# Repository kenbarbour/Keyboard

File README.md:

# Keyboard
Source files for building some mechanical keyboards

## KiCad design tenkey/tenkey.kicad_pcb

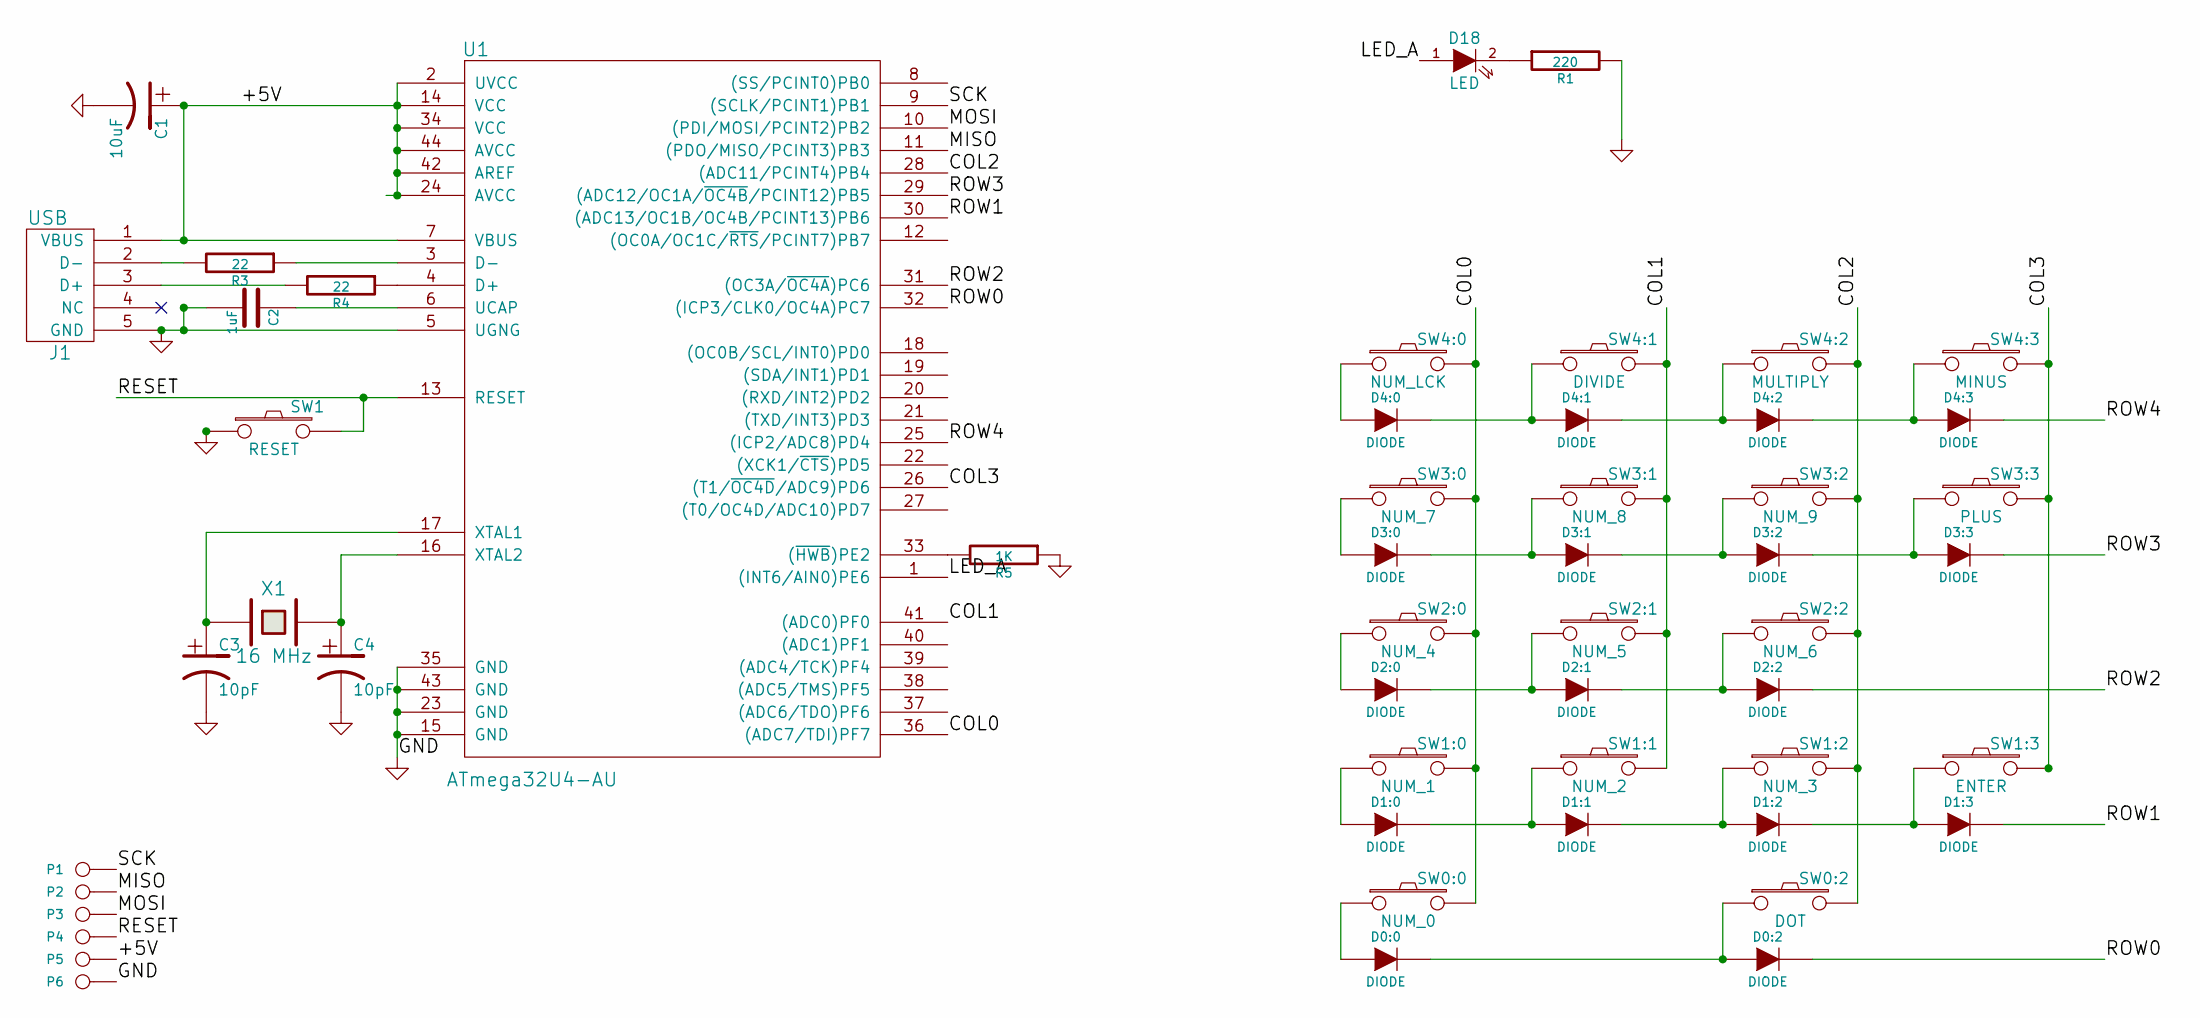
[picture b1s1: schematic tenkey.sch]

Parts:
C1: 10uF
C2: 1uF
C3, C4: 10pF
D0:0, D0:2, D1:0, D1:1, D1:2, D1:3, D2:0, D2:1, D2:2, D3:0, D3:1, D3:2, D3:3, D4:0, D4:1, D4:2, D4:3: DIODE
D18: LED
J1: USB
P1: SCK
P2: MISO
P3: MOSI
P4: RESET
P5: 5V
P6: GND
R1: 220
R3, R4: 22
R5: 1K
SW0:0: NUM_0
SW0:2: DOT
SW1: RESET
SW1:0: NUM_1
SW1:1: NUM_2
SW1:2: NUM_3
SW1:3: ENTER
SW2:0: NUM_4
SW2:1: NUM_5
SW2:2: NUM_6
SW3:0: NUM_7
SW3:1: NUM_8
SW3:2: NUM_9
SW3:3: PLUS
SW4:0: NUM_LCK
SW4:1: DIVIDE
SW4:2: MULTIPLY
SW4:3: MINUS
U1: ATmega32U4-AU
X1: 16 MHz

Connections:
/+5V: C1.1, J1.1 (VBUS), P5.1, U1.2 (UVCC), U1.7 (VBUS), U1.14 (VCC), U1.24 (AVCC), U1.34 (VCC), U1.42 (AREF), U1.44 (AVCC)
/COL0: SW0:0.2, SW1:0.2, SW2:0.2, SW3:0.2, SW4:0.2, U1.36 ((ADC7/TDI)PF7)
/COL1: SW1:1.2, SW2:1.2, SW3:1.2, SW4:1.2, U1.41 ((ADC0)PF0)
/COL2: SW0:2.2, SW1:2.2, SW2:2.2, SW3:2.2, SW4:2.2, U1.28 ((ADC11/PCINT4)PB4)
/COL3: SW1:3.2, SW3:3.2, SW4:3.2, U1.26 ((T1/~OC4D~/ADC9)PD6)
/LED_A: D18.1 (A), U1.1 ((INT6/AIN0)PE6)
/MISO: P2.1, U1.11 ((PDO/MISO/PCINT3)PB3)
/MOSI: P3.1, U1.10 ((PDI/MOSI/PCINT2)PB2)
/RESET: P4.1, SW1.2, U1.13 (RESET)
/ROW0: D0:2.2 (K), U1.32 ((ICP3/CLK0/OC4A)PC7)
/ROW1: D1:3.2 (K), U1.30 ((ADC13/OC1B/OC4B/PCINT13)PB6)
/ROW2: D2:2.2 (K), U1.31 ((OC3A/~OC4A~)PC6)
/ROW3: D3:3.2 (K), U1.29 ((ADC12/OC1A/~OC4B~/PCINT12)PB5)
/ROW4: D4:3.2 (K), U1.25 ((ICP2/ADC8)PD4)
/SCK: P1.1, U1.9 ((SCLK/PCINT1)PB1)
GND: C1.2, C2.2, C3.2, C4.2, J1.5 (GND), P6.1, R1.2, R5.1, SW1.1, U1.5 (UGNG), U1.15 (GND), U1.23 (GND), U1.35 (GND), U1.43 (GND)
unnamed: C2.1, U1.6 (UCAP)
unnamed: C3.1, U1.17 (XTAL1), X1.1
unnamed: C4.1, U1.16 (XTAL2), X1.2
unnamed: D0:0.1 (A), SW0:0.1
unnamed: D0:0.2 (K), D0:2.1 (A), SW0:2.1
unnamed: D1:0.1 (A), SW1:0.1
unnamed: D1:0.2 (K), D1:1.1 (A), SW1:1.1
unnamed: D1:1.2 (K), D1:2.1 (A), SW1:2.1
unnamed: D1:2.2 (K), D1:3.1 (A), SW1:3.1
unnamed: D2:0.1 (A), SW2:0.1
unnamed: D2:0.2 (K), D2:1.1 (A), SW2:1.1
unnamed: D2:1.2 (K), D2:2.1 (A), SW2:2.1
unnamed: D3:0.1 (A), SW3:0.1
unnamed: D3:0.2 (K), D3:1.1 (A), SW3:1.1
unnamed: D3:1.2 (K), D3:2.1 (A), SW3:2.1
unnamed: D3:2.2 (K), D3:3.1 (A), SW3:3.1
unnamed: D4:0.1 (A), SW4:0.1
unnamed: D4:0.2 (K), D4:1.1 (A), SW4:1.1
unnamed: D4:1.2 (K), D4:2.1 (A), SW4:2.1
unnamed: D4:2.2 (K), D4:3.1 (A), SW4:3.1
unnamed: D18.2 (K), R1.1
unnamed: J1.2 (D-), R3.2
unnamed: J1.3 (D+), R4.2
unnamed: R3.1, U1.3 (D-)
unnamed: R4.1, U1.4 (D+)
unnamed: R5.2, U1.33 ((~HWB~)PE2)

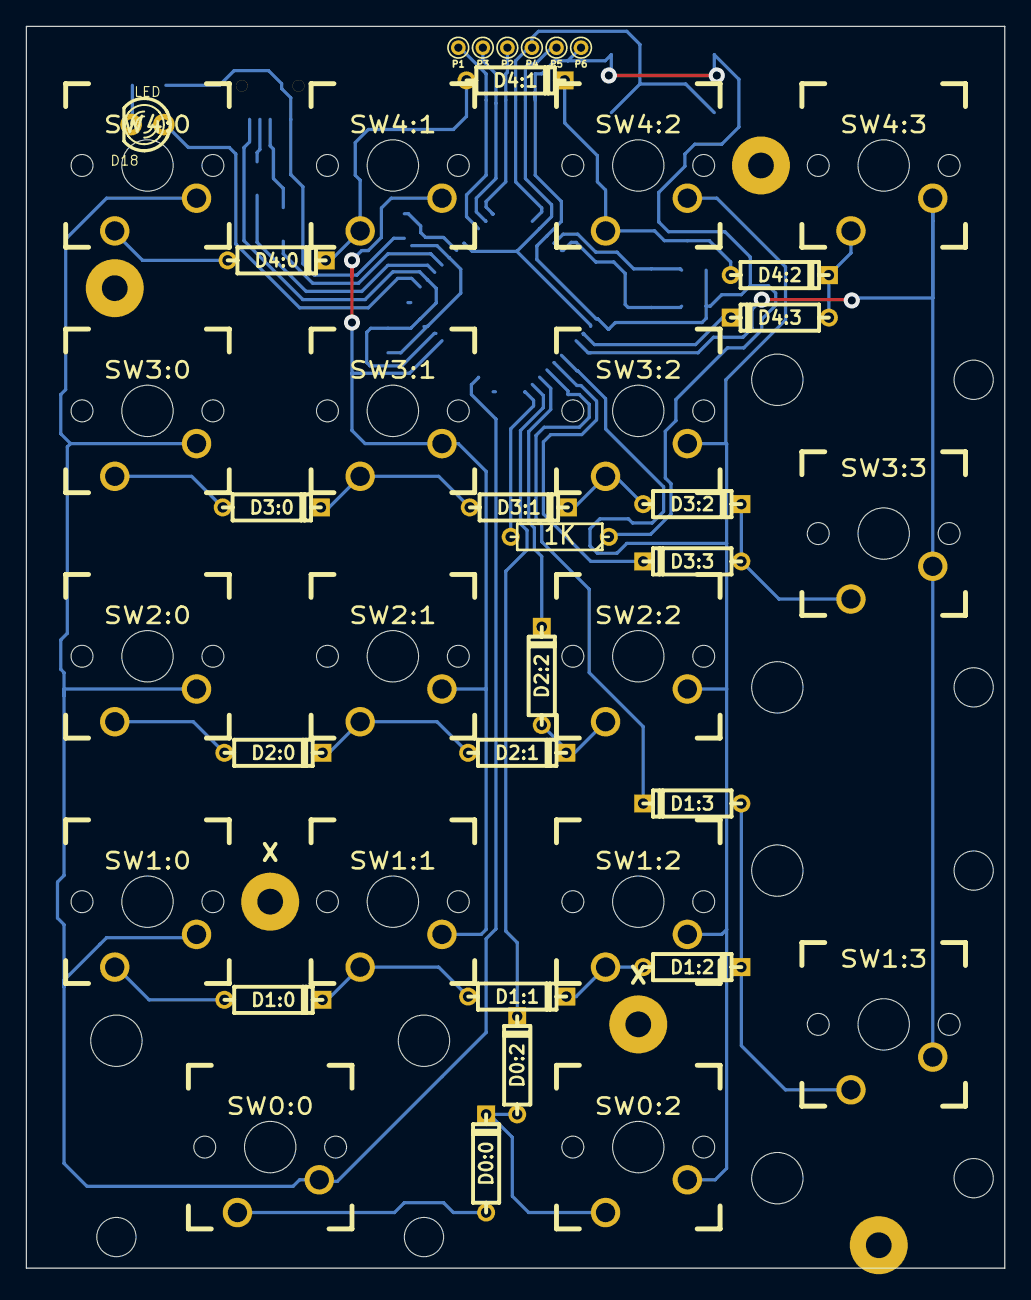
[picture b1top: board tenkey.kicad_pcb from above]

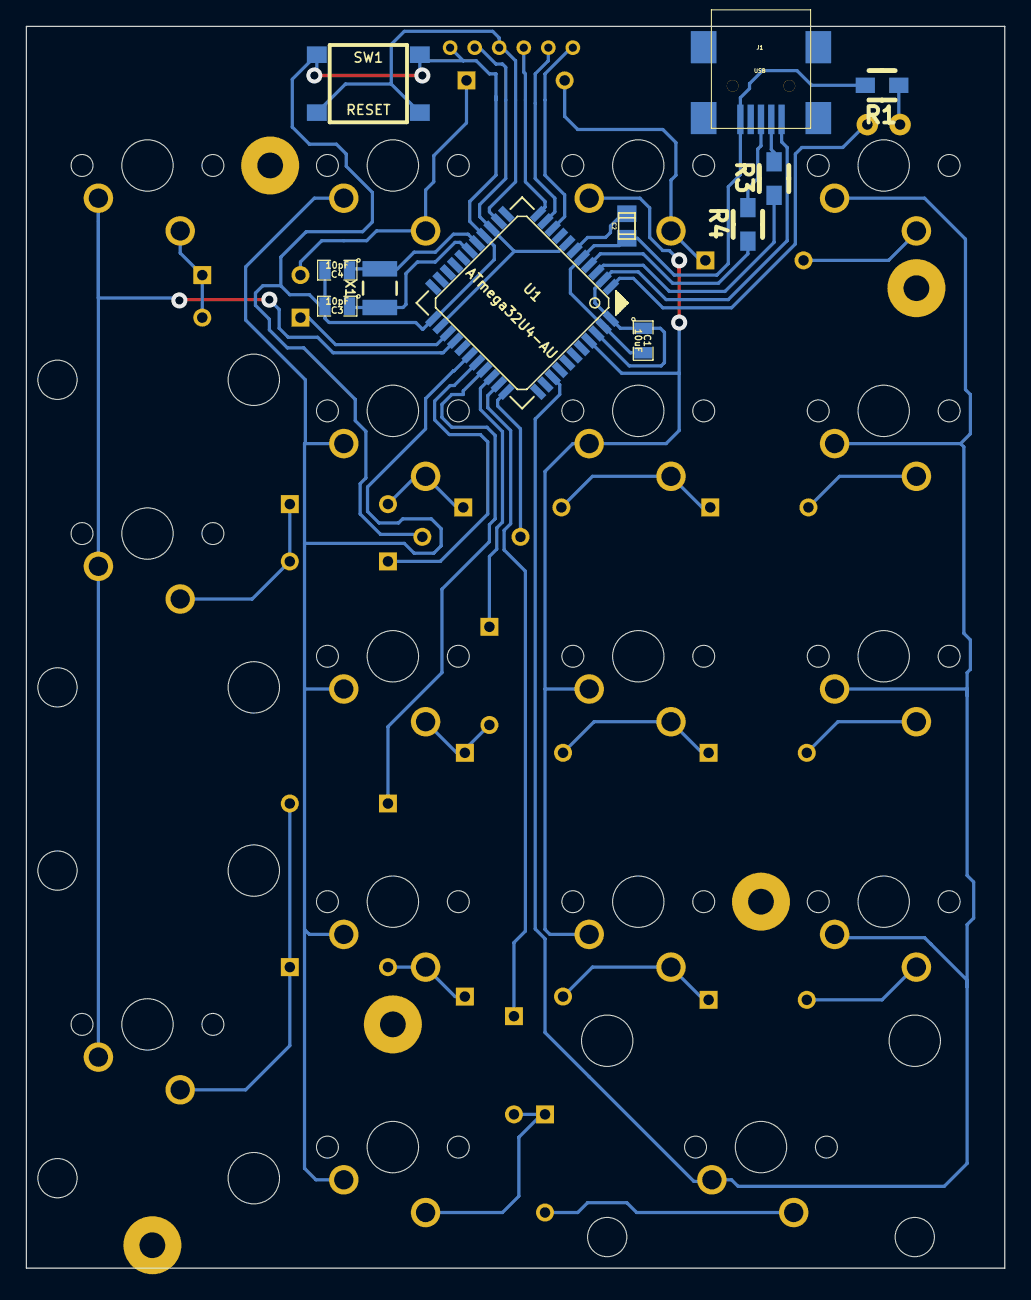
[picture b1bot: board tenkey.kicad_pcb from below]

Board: 2 copper layers, 75.9 x 96.4 mm, 55 parts (11 on the bottom side), 42 nets.

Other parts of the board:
X: SolderWirePad_single_2mmDrill
X#2: SolderWirePad_single_2mmDrill

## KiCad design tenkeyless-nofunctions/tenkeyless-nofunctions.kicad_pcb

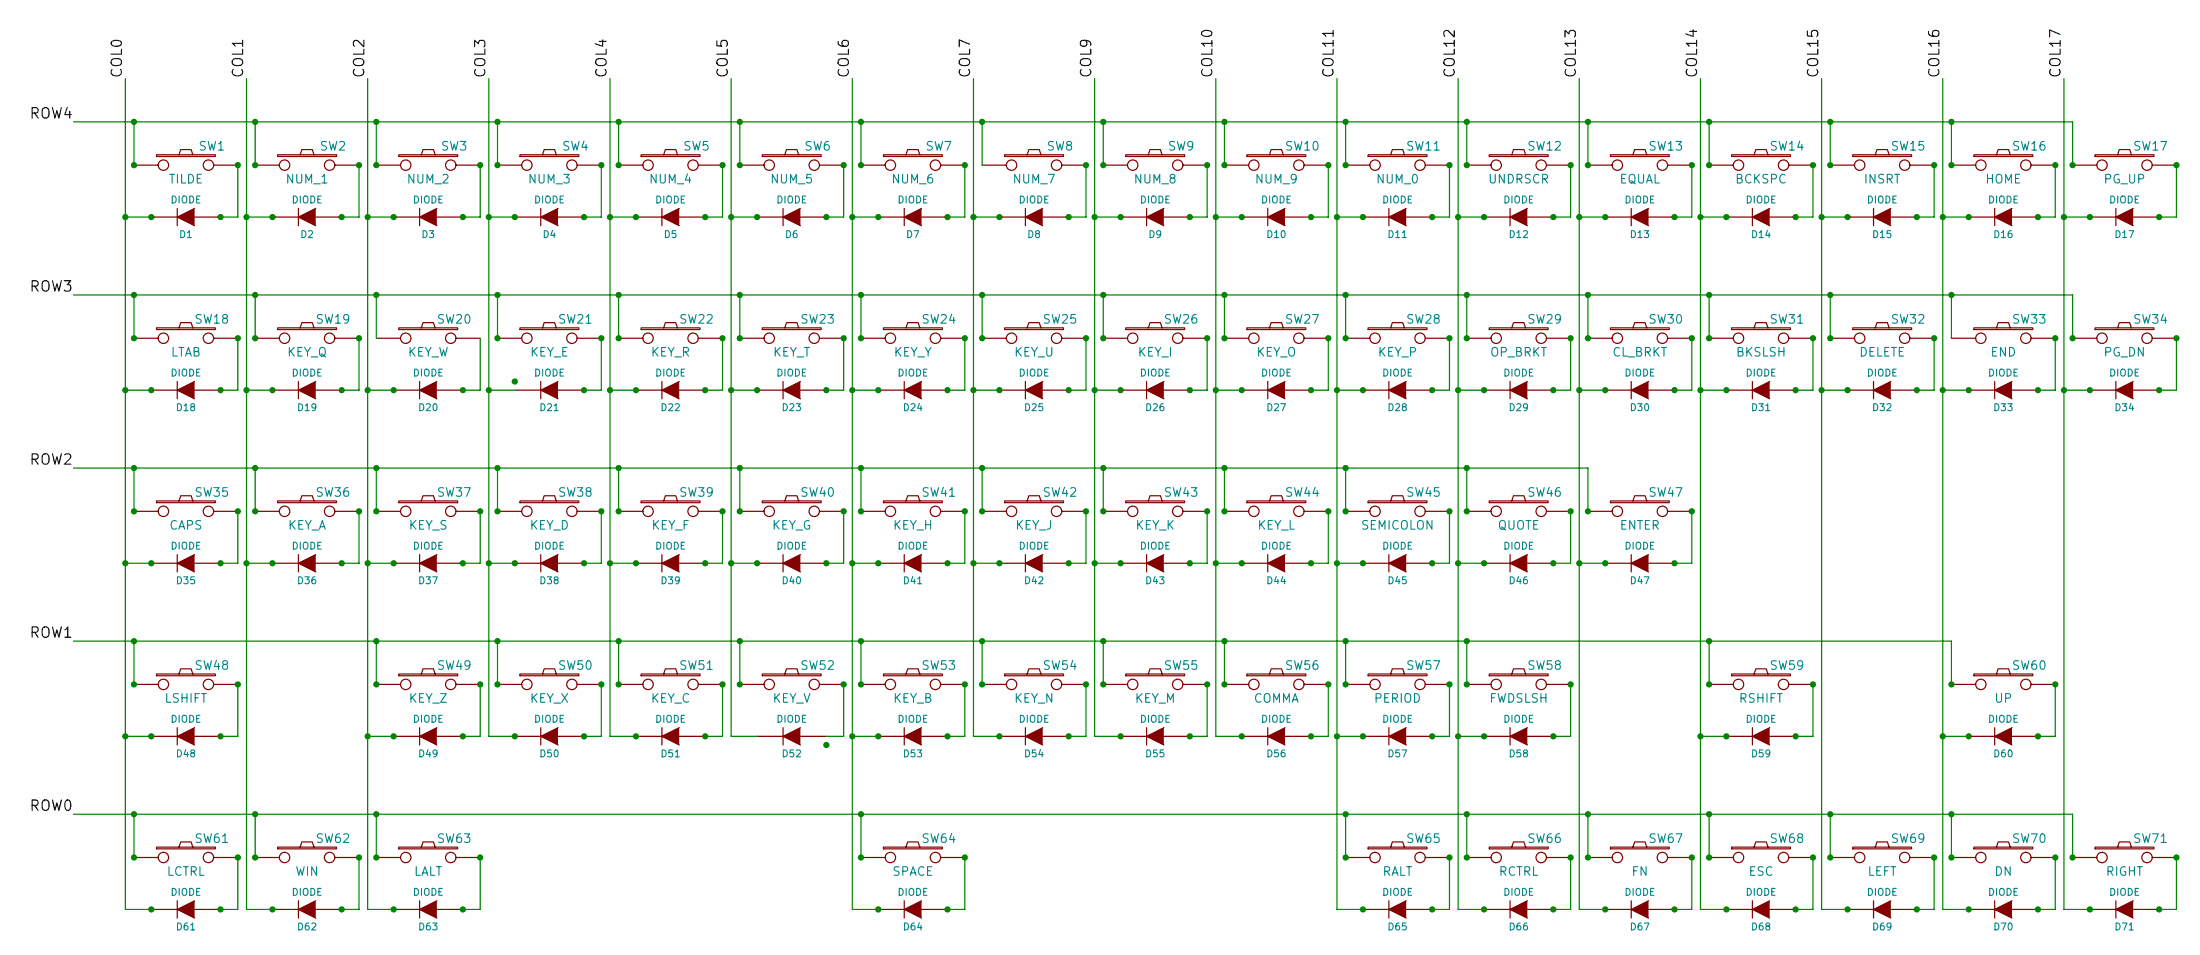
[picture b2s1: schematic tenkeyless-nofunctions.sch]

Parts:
D1, D2, D3, D4, D5, D6, D7, D8, D9, D10, D11, D12, D13, D14, D15, D16, D17, D18, D19, D20, D21, D22, D23, D24, D25, D26, D27, D28, D29, D30, D31, D32, D33, D34, D35, D36, D37, D38, D39, D40, D41, D42, D43, D44, D45, D46, D47, D48, D49, D50, D51, D52, D53, D54, D55, D56, D57, D58, D59, D60, D61, D62, D63, D64, D65, D66, D67, D68, D69, D70, D71: DIODE
SW1: TILDE
SW2: NUM_1
SW3: NUM_2
SW4: NUM_3
SW5: NUM_4
SW6: NUM_5
SW7: NUM_6
SW8: NUM_7
SW9: NUM_8
SW10: NUM_9
SW11: NUM_0
SW12: UNDRSCR
SW13: EQUAL
SW14: BCKSPC
SW15: INSRT
SW16: HOME
SW17: PG_UP
SW18: LTAB
SW19: KEY_Q
SW20: KEY_W
SW21: KEY_E
SW22: KEY_R
SW23: KEY_T
SW24: KEY_Y
SW25: KEY_U
SW26: KEY_I
SW27: KEY_O
SW28: KEY_P
SW29: OP_BRKT
SW30: CL_BRKT
SW31: BKSLSH
SW32: DELETE
SW33: END
SW34: PG_DN
SW35: CAPS
SW36: KEY_A
SW37: KEY_S
SW38: KEY_D
SW39: KEY_F
SW40: KEY_G
SW41: KEY_H
SW42: KEY_J
SW43: KEY_K
SW44: KEY_L
SW45: SEMICOLON
SW46: QUOTE
SW47: ENTER
SW48: LSHIFT
SW49: KEY_Z
SW50: KEY_X
SW51: KEY_C
SW52: KEY_V
SW53: KEY_B
SW54: KEY_N
SW55: KEY_M
SW56: COMMA
SW57: PERIOD
SW58: FWDSLSH
SW59: RSHIFT
SW60: UP
SW61: LCTRL
SW62: WIN
SW63: LALT
SW64: SPACE
SW65: RALT
SW66: RCTRL
SW67: FN
SW68: ESC
SW69: LEFT
SW70: DN
SW71: RIGHT

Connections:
/COL0: D1.2 (K), D18.2 (K), D35.2 (K), D48.2 (K), D61.2 (K)
/COL1: D2.2 (K), D19.2 (K), D36.2 (K), D62.2 (K)
/COL2: D3.2 (K), D20.2 (K), D37.2 (K), D49.2 (K), D63.2 (K)
/COL3: D4.2 (K), D21.2 (K), D38.2 (K), D50.2 (K)
/COL4: D5.2 (K), D22.2 (K), D39.2 (K), D51.2 (K)
/COL5: D6.2 (K), D23.2 (K), D40.2 (K), D52.2 (K)
/COL6: D7.2 (K), D24.2 (K), D41.2 (K), D53.2 (K), D64.2 (K)
/COL7: D8.2 (K), D25.2 (K), D42.2 (K), D54.2 (K)
/COL9: D9.2 (K), D26.2 (K), D43.2 (K), D55.2 (K)
/COL10: D10.2 (K), D27.2 (K), D44.2 (K), D56.2 (K)
/COL11: D11.2 (K), D28.2 (K), D45.2 (K), D57.2 (K), D65.2 (K)
/COL12: D12.2 (K), D29.2 (K), D46.2 (K), D58.2 (K), D66.2 (K)
/COL13: D13.2 (K), D30.2 (K), D47.2 (K), D67.2 (K)
/COL14: D14.2 (K), D31.2 (K), D59.2 (K), D68.2 (K)
/COL15: D15.2 (K), D32.2 (K), D69.2 (K)
/COL16: D16.2 (K), D33.2 (K), D60.2 (K), D70.2 (K)
/COL17: D17.2 (K), D34.2 (K), D71.2 (K)
/ROW0: SW61.1, SW62.1, SW63.1, SW64.1, SW65.1, SW66.1, SW67.1, SW68.1, SW69.1, SW70.1, SW71.1
/ROW1: SW48.1, SW49.1, SW50.1, SW51.1, SW52.1, SW53.1, SW54.1, SW55.1, SW56.1, SW57.1, SW58.1, SW59.1, SW60.1
/ROW2: SW35.1, SW36.1, SW37.1, SW38.1, SW39.1, SW40.1, SW41.1, SW42.1, SW43.1, SW44.1, SW45.1, SW46.1, SW47.1
/ROW3: SW18.1, SW19.1, SW20.1, SW21.1, SW22.1, SW23.1, SW24.1, SW25.1, SW26.1, SW27.1, SW28.1, SW29.1, SW30.1, SW31.1, SW32.1, SW33.1, SW34.1
/ROW4: SW1.1, SW2.1, SW3.1, SW4.1, SW5.1, SW6.1, SW7.1, SW8.1, SW9.1, SW10.1, SW11.1, SW12.1, SW13.1, SW14.1, SW15.1, SW16.1, SW17.1
unnamed: D1.1 (A), SW1.2
unnamed: D2.1 (A), SW2.2
unnamed: D3.1 (A), SW3.2
unnamed: D4.1 (A), SW4.2
unnamed: D5.1 (A), SW5.2
unnamed: D6.1 (A), SW6.2
unnamed: D7.1 (A), SW7.2
unnamed: D8.1 (A), SW8.2
unnamed: D9.1 (A), SW9.2
unnamed: D10.1 (A), SW10.2
unnamed: D11.1 (A), SW11.2
unnamed: D12.1 (A), SW12.2
unnamed: D13.1 (A), SW13.2
unnamed: D14.1 (A), SW14.2
unnamed: D15.1 (A), SW15.2
unnamed: D16.1 (A), SW16.2
unnamed: D17.1 (A), SW17.2
unnamed: D18.1 (A), SW18.2
unnamed: D19.1 (A), SW19.2
unnamed: D20.1 (A), SW20.2
unnamed: D21.1 (A), SW21.2
unnamed: D22.1 (A), SW22.2
unnamed: D23.1 (A), SW23.2
unnamed: D24.1 (A), SW24.2
unnamed: D25.1 (A), SW25.2
unnamed: D26.1 (A), SW26.2
unnamed: D27.1 (A), SW27.2
unnamed: D28.1 (A), SW28.2
unnamed: D29.1 (A), SW29.2
unnamed: D30.1 (A), SW30.2
unnamed: D31.1 (A), SW31.2
unnamed: D32.1 (A), SW32.2
unnamed: D33.1 (A), SW33.2
unnamed: D34.1 (A), SW34.2
unnamed: D35.1 (A), SW35.2
unnamed: D36.1 (A), SW36.2
unnamed: D37.1 (A), SW37.2
unnamed: D38.1 (A), SW38.2
unnamed: D39.1 (A), SW39.2
unnamed: D40.1 (A), SW40.2
unnamed: D41.1 (A), SW41.2
unnamed: D42.1 (A), SW42.2
unnamed: D43.1 (A), SW43.2
unnamed: D44.1 (A), SW44.2
unnamed: D45.1 (A), SW45.2
unnamed: D46.1 (A), SW46.2
unnamed: D47.1 (A), SW47.2
unnamed: D48.1 (A), SW48.2
unnamed: D49.1 (A), SW49.2
unnamed: D50.1 (A), SW50.2
unnamed: D51.1 (A), SW51.2
unnamed: D52.1 (A), SW52.2
unnamed: D53.1 (A), SW53.2
unnamed: D54.1 (A), SW54.2
unnamed: D55.1 (A), SW55.2
unnamed: D56.1 (A), SW56.2
unnamed: D57.1 (A), SW57.2
unnamed: D58.1 (A), SW58.2
unnamed: D59.1 (A), SW59.2
unnamed: D60.1 (A), SW60.2
unnamed: D61.1 (A), SW61.2
unnamed: D62.1 (A), SW62.2
unnamed: D63.1 (A), SW63.2
unnamed: D64.1 (A), SW64.2
unnamed: D65.1 (A), SW65.2
unnamed: D66.1 (A), SW66.2
unnamed: D67.1 (A), SW67.2
unnamed: D68.1 (A), SW68.2
unnamed: D69.1 (A), SW69.2
unnamed: D70.1 (A), SW70.2
unnamed: D71.1 (A), SW71.2

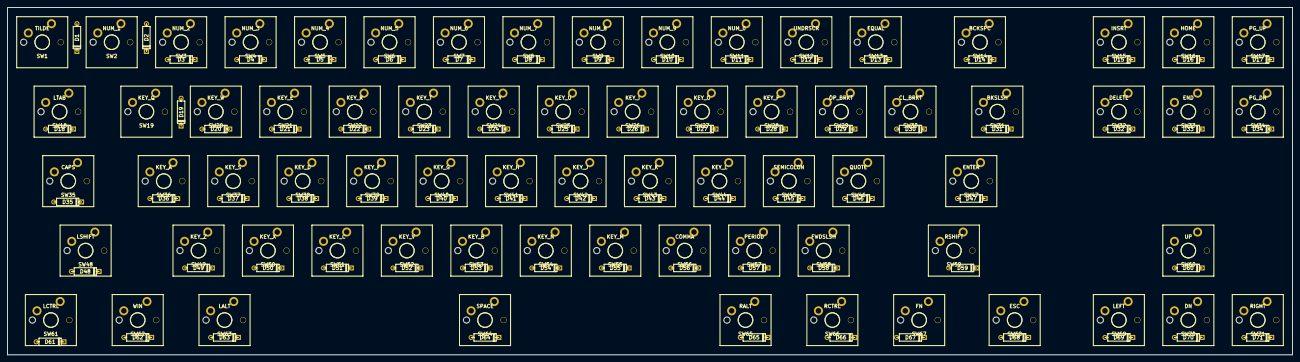
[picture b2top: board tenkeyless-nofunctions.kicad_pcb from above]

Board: 2 copper layers, 352.4 x 95.2 mm, 142 parts (0 on the bottom side), 93 nets.

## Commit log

2016-03-24 Added a template for a 60% layout
2016-03-24 made some small layouts and schematics for a tenkeyless layout without function row
2016-03-30 started a layout for a tenkeyless without the function row
2016-03-31 flipped keymodule pins; now gotta figure out routing with as few jumps as possible
2016-04-01 did some organizing of the files before this got any more out of hand
2016-04-01 lib to contain all the components
2016-04-01 we're going to have to switch to the Teensie2.0++
2016-04-01 new tenkey board
2016-04-02 hopefully have a working schematic
2016-04-02 tenkey footprints associated, except teensie
2016-04-02 pcb has button holes
2016-04-02 Fixed pinout on the Teensy2.0 module and updated the tenkey schematic/board
2016-04-05 apparently, you need some space between the keyswitches to make room for the caps
2016-04-05 fixed the vertical 2 unit switch footprint and routed some tenkey
2016-04-06 tenkey routed except for row/cols to teensy
2016-04-06 tenkey finished pcb routing and adjusting pinout
2016-04-07 starting the embedding of a ATMega32U4 on the tenkey instead of a teensy
2016-04-18 teensie is gone, were building this with the straight ATMega32u4
2016-04-21 changed some footprints to SMD
2016-04-21 somehow managed to get most everything routed with only 1 jumper (and possibly 1 more)
2016-04-22 PCB routing done, needs to check and reconcile footprints before ordering components
2016-04-27 larger vias and moved diodes out of area reserved for switches
2016-04-27 connected ROW2 and ROW3 to ATMEGA32U4 and added mounting holes
2016-04-28 moved some close traces
